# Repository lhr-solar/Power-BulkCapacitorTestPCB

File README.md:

# Power-BulkCapacitorTestPCB
PCB with bulk output capacitance to simulate capacitive loads like the motor controller

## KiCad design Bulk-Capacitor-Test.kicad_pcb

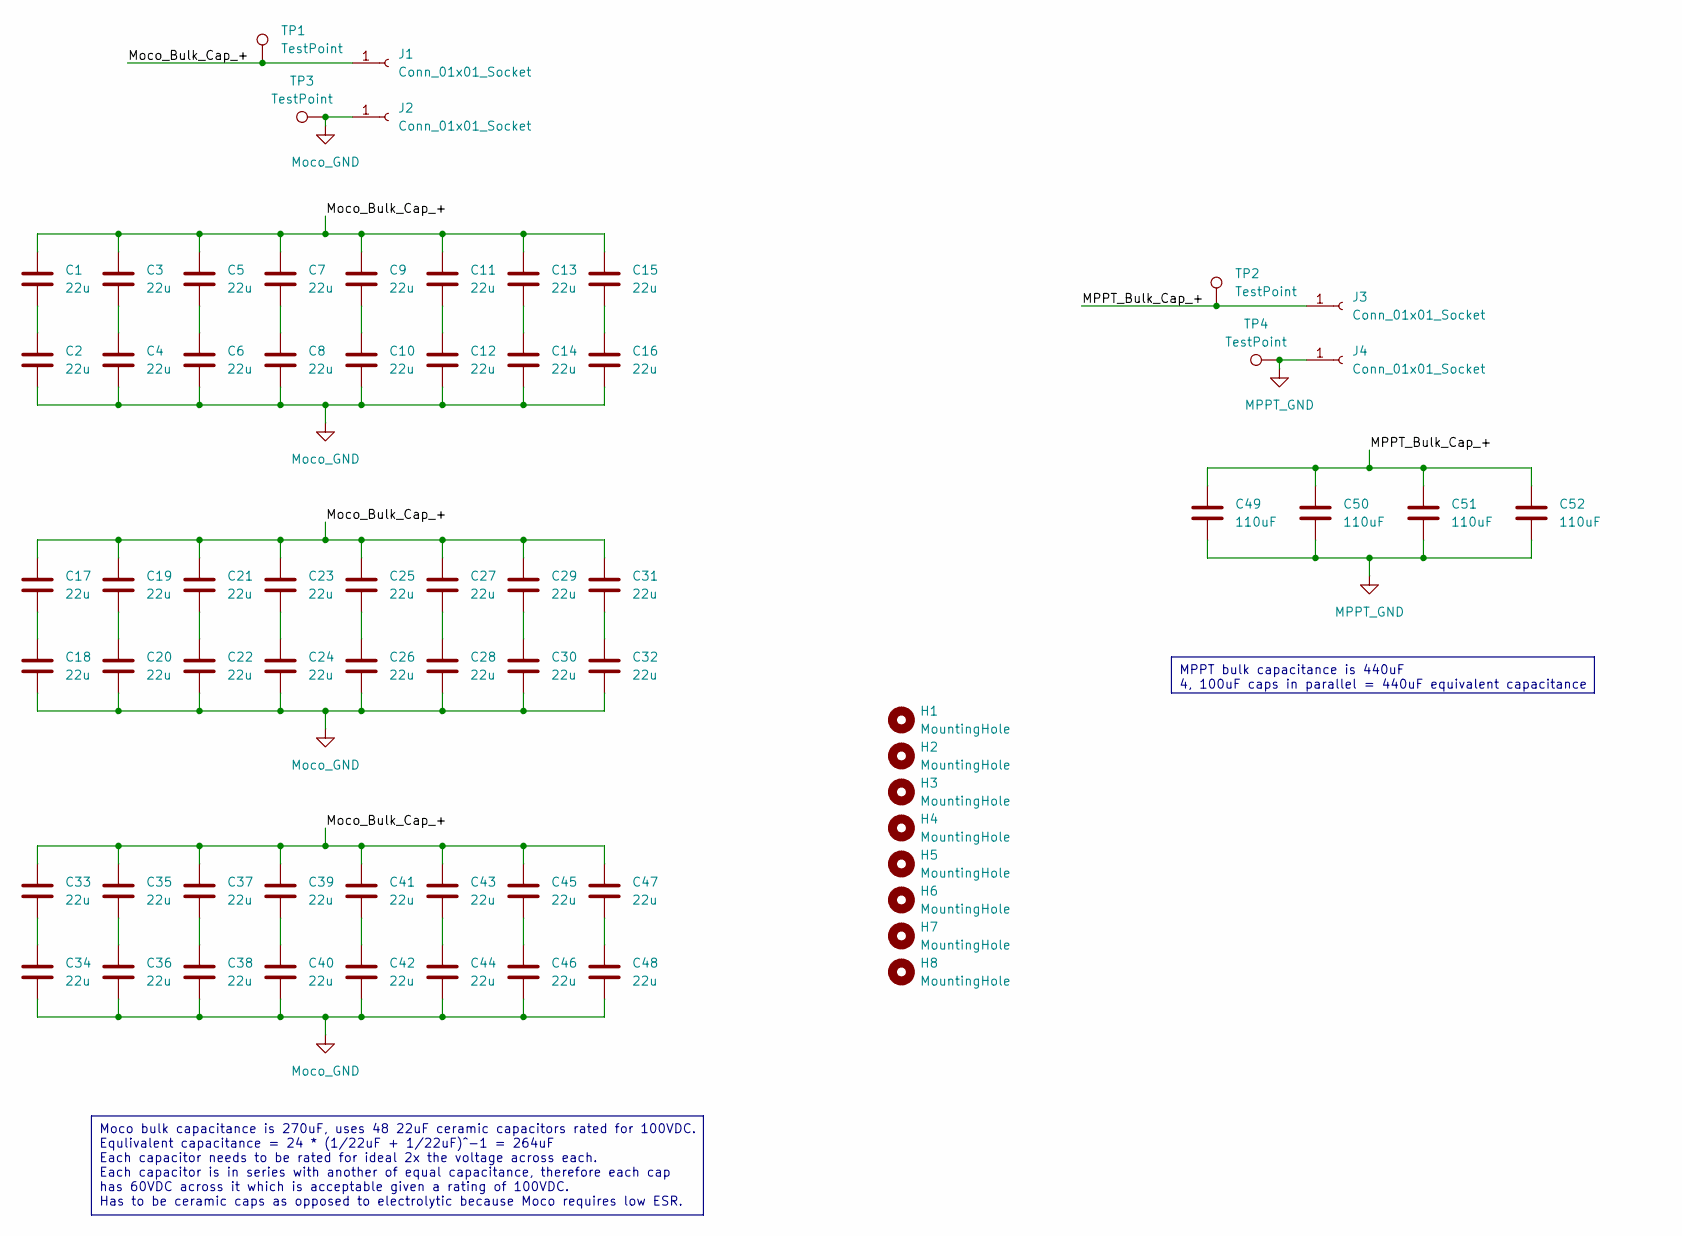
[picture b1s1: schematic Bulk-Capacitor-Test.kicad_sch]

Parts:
C1, C2, C3, C4, C5, C6, C7, C8, C9, C10, C11, C12, C13, C14, C15, C16, C17, C18, C19, C20, C21, C22, C23, C24, C25, C26, C27, C28, C29, C30, C31, C32, C33, C34, C35, C36, C37, C38, C39, C40, C41, C42, C43, C44, C45, C46, C47, C48: 22u; C_2220_5750Metric
C49, C50, C51, C52: 110uF; CAPPRD750W80D1825H2800
H1, H2, H3, H4, H5, H6, H7, H8: MountingHole; MountingHole_3mm
J1, J2, J3, J4: Conn_01x01_Socket; 5754
TP1, TP2, TP3, TP4: TestPoint; 5281

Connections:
/MPPT_Bulk_Cap_+: C49.1, C50.1, C51.1, C52.1, J3.1, TP2.1
/Moco_Bulk_Cap_+: C1.1, C3.1, C5.1, C7.1, C9.1, C11.1, C13.1, C15.1, C17.1, C19.1, C21.1, C23.1, C25.1, C27.1, C29.1, C31.1, C33.1, C35.1, C37.1, C39.1, C41.1, C43.1, C45.1, C47.1, J1.1, TP1.1
MPPT_GND: C49.2, C50.2, C51.2, C52.2, J4.1, TP4.1
Moco_GND: C2.2, C4.2, C6.2, C8.2, C10.2, C12.2, C14.2, C16.2, C18.2, C20.2, C22.2, C24.2, C26.2, C28.2, C30.2, C32.2, C34.2, C36.2, C38.2, C40.2, C42.2, C44.2, C46.2, C48.2, J2.1, TP3.1
unnamed: C1.2, C2.1
unnamed: C3.2, C4.1
unnamed: C5.2, C6.1
unnamed: C7.2, C8.1
unnamed: C9.2, C10.1
unnamed: C11.2, C12.1
unnamed: C13.2, C14.1
unnamed: C15.2, C16.1
unnamed: C17.2, C18.1
unnamed: C19.2, C20.1
unnamed: C21.2, C22.1
unnamed: C23.2, C24.1
unnamed: C25.2, C26.1
unnamed: C27.2, C28.1
unnamed: C29.2, C30.1
unnamed: C31.2, C32.1
unnamed: C33.2, C34.1
unnamed: C35.2, C36.1
unnamed: C37.2, C38.1
unnamed: C39.2, C40.1
unnamed: C41.2, C42.1
unnamed: C43.2, C44.1
unnamed: C45.2, C46.1
unnamed: C47.2, C48.1

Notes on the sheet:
Moco bulk capacitance is 270uF, uses 48 22uF ceramic capacitors rated for 100VDC. Equlivalent capacitance = 24 * (1/22uF + 1/22uF)^-1 = 264uF Each capacitor needs to be rated for ideal 2x the voltage across each. Each capacitor is in series with another of equal capacitance, therefore each cap has 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
MPPT bulk capacitance is 440uF 4, 100uF caps in parallel = 440uF equivalent capacitance

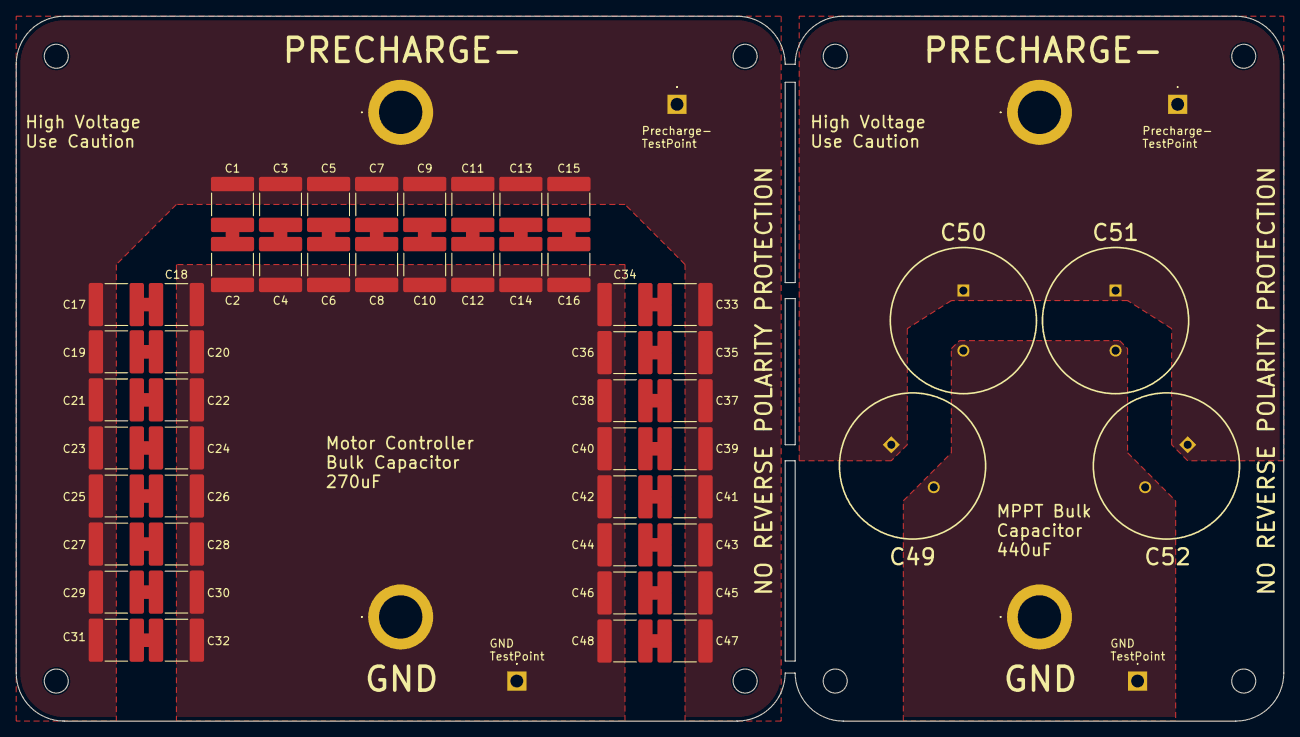
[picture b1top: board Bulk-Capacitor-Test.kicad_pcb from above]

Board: 2 copper layers, 158.2 x 88.0 mm, 68 parts (0 on the bottom side), 28 nets.

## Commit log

2025-03-27 pcb finished for ravi review
2025-03-28 added testpoints
2025-03-28 now two boards
